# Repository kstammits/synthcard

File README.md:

# sc_Examples
demo and public synthcards

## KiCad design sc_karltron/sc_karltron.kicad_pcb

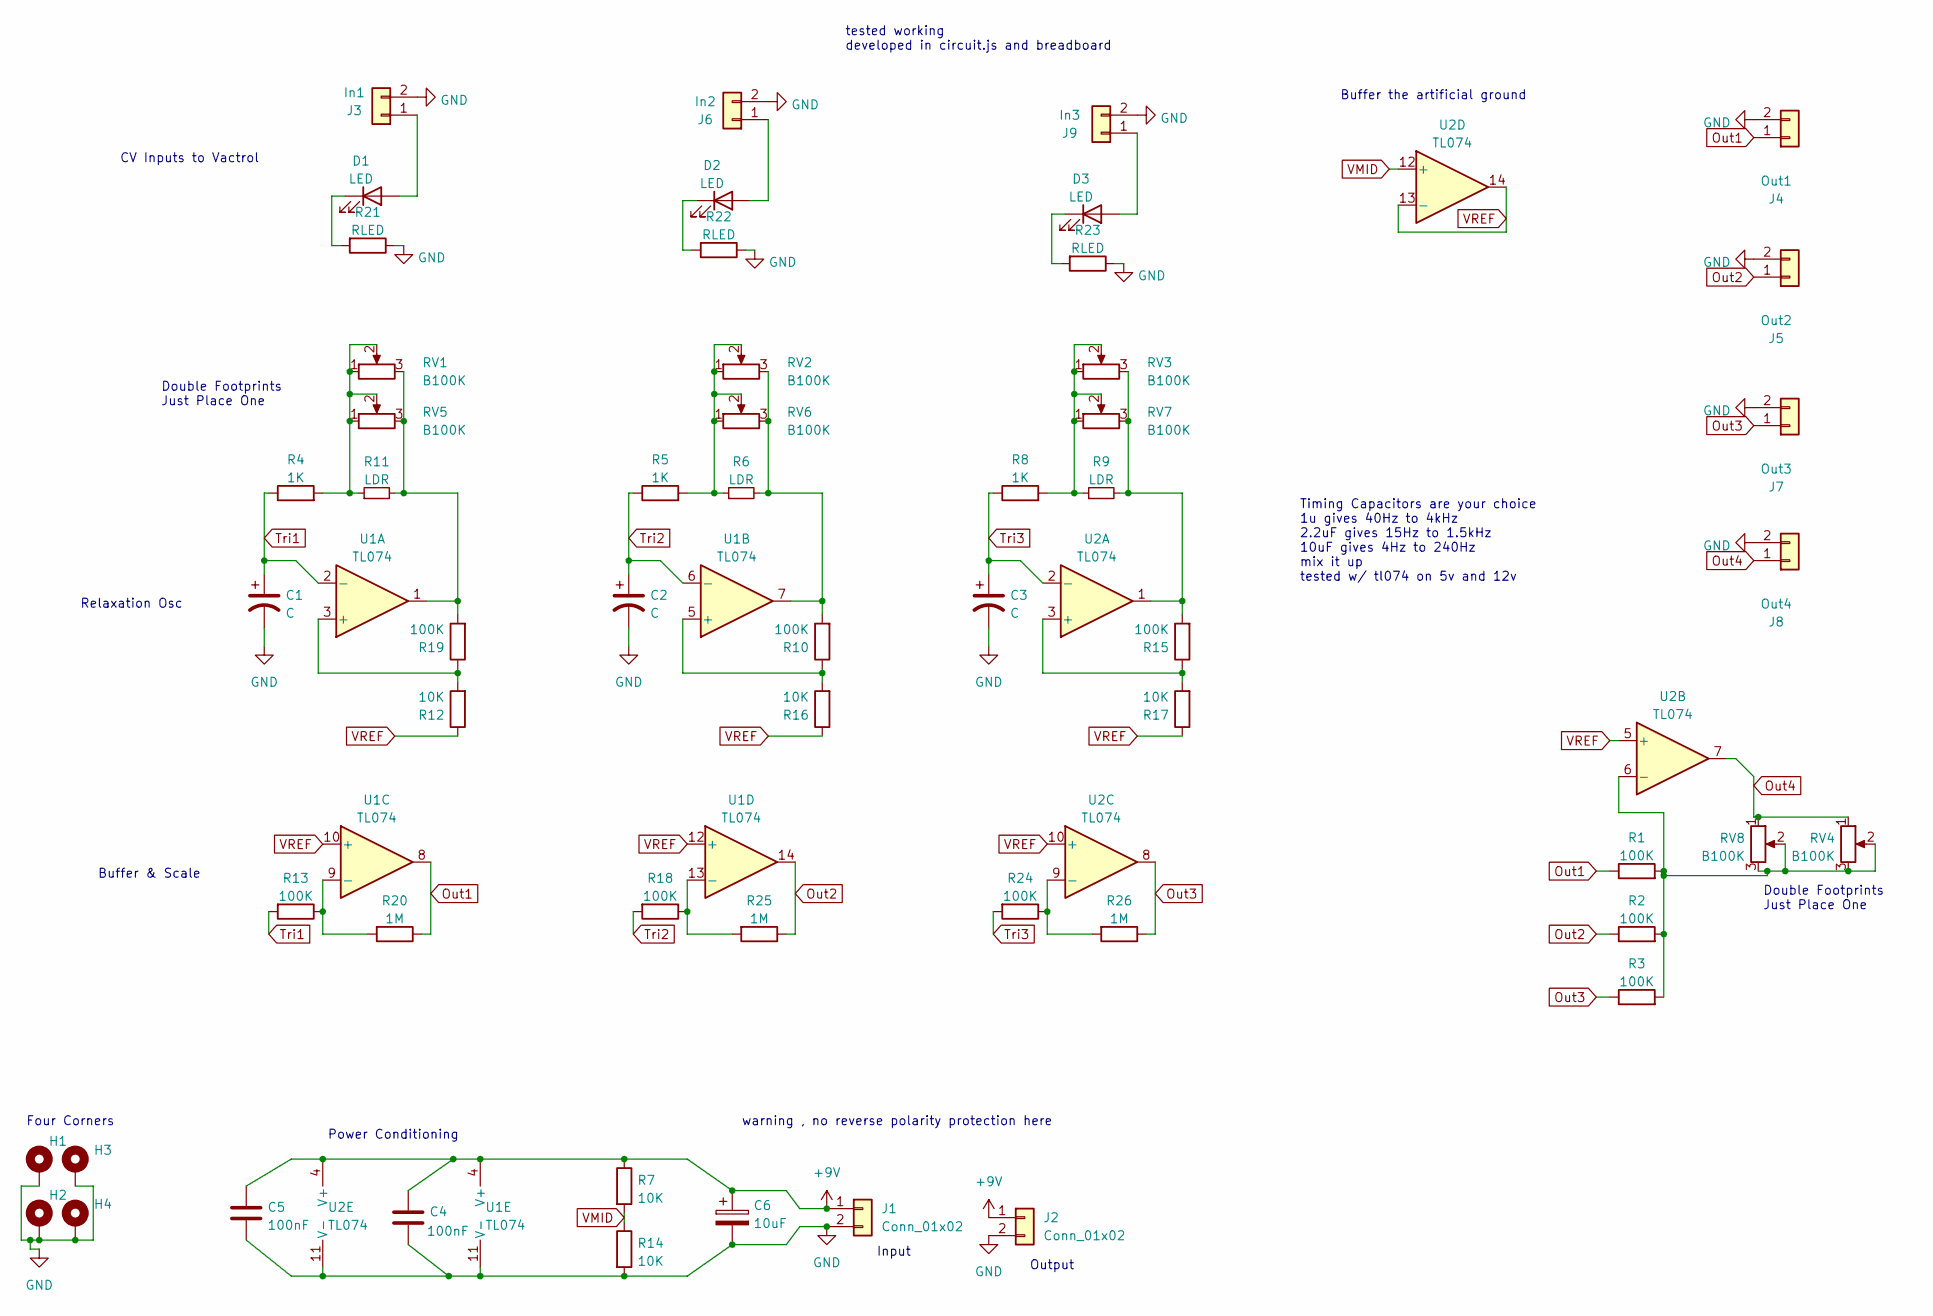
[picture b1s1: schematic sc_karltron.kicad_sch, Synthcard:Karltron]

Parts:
C1, C2, C3: C; C_Disc_D5.0mm_W2.5mm_P5.00mm
C4, C5: 100nF; C_Disc_D5.0mm_W2.5mm_P5.00mm
C6: 10uF; CP_Radial_D5.0mm_P2.50mm
D1, D2, D3: LED; LED_D5.0mm_Horizontal_O3.81mm_Z3.0mm
H1, H2, H3, H4: MountingHole_Pad; MountingHole_3.2mm_M3_Pad
J1, J2: Conn_01x02; PinHeader_1x02_P2.54mm_Horizontal
J3: In1; PinHeader_1x02_P2.54mm_Vertical
J4: Out1; PinHeader_1x02_P2.54mm_Vertical
J5: Out2; PinHeader_1x02_P2.54mm_Vertical
J6: In2; PinHeader_1x02_P2.54mm_Vertical
J7: Out3; PinHeader_1x02_P2.54mm_Vertical
J8: Out4; PinHeader_1x02_P2.54mm_Vertical
J9: In3; PinHeader_1x02_P2.54mm_Vertical
R1, R2, R3, R10, R13, R15, R18, R19, R24: 100K; R_Axial_DIN0207_L6.3mm_D2.5mm_P10.16mm_Horizontal
R4, R5, R8: 1K; R_Axial_DIN0207_L6.3mm_D2.5mm_P10.16mm_Horizontal
R6, R9, R11: LDR; R_Axial_DIN0204_L3.6mm_D1.6mm_P5.08mm_Horizontal
R7, R12, R14, R16, R17: 10K; R_Axial_DIN0207_L6.3mm_D2.5mm_P10.16mm_Horizontal
R20, R25, R26: 1M; R_Axial_DIN0207_L6.3mm_D2.5mm_P10.16mm_Horizontal
R21, R22, R23: RLED; R_Axial_DIN0207_L6.3mm_D2.5mm_P10.16mm_Horizontal
RV1, RV2, RV3, RV4: B100K; Potentiometer_ACP_CA9-H5_Horizontal
RV5, RV6, RV7, RV8: B100K; Potentiometer_Alpha_RD901F-40-00D_Single_Vertical
U1, U2: TL074; DIP-14_W7.62mm

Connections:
+9V: C4.1, C5.1, C6.1, J1.1, J2.1, R7.1, U1.4 (V+), U2.4 (V+)
GND: C1.2, C2.2, C3.2, C4.2, C5.2, C6.2, H1.1, H2.1, H3.1, H4.1, J1.2, J2.2, J3.2, J4.2, J5.2, J6.2, J7.2, J8.2, J9.2, R14.2, R21.1, R22.1, R23.1, U1.11 (V-), U2.11 (V-)
unnamed: D1.1 (K), R21.2
unnamed: D1.2 (A), J3.1
unnamed: D2.1 (K), R22.2
unnamed: D2.2 (A), J6.1
unnamed: D3.1 (K), R23.2
unnamed: D3.2 (A), J9.1
unnamed: R1.2, R2.2, R3.2, RV4.2, RV4.3, RV8.2, RV8.3, U2.6 (-)
unnamed: R5.2, R6.1, RV2.1, RV2.2, RV6.1, RV6.2
unnamed: R8.2, R9.1, RV3.1, RV3.2, RV7.1, RV7.2
unnamed: R12.2, R19.1, U1.3 (+)
unnamed: R13.1, R20.2, U1.9 (-)
unnamed: R4.2, R11.1, RV1.1, RV1.2, RV5.1, RV5.2
unnamed: R11.2, R19.2, RV1.3, RV5.3, U1.1
unnamed: R10.1, R16.2, U1.5 (+)
unnamed: R6.2, R10.2, RV2.3, RV6.3, U1.7
unnamed: R18.1, R25.2, U1.13 (-)
unnamed: R9.2, R15.2, RV3.3, RV7.3, U2.1
unnamed: R15.1, R17.2, U2.3 (+)
unnamed: R24.1, R26.2, U2.9 (-)
Out1: J4.1, R1.1, R20.1, U1.8
Out2: J5.1, R2.1, R25.1, U1.14
Out3: J7.1, R3.1, R26.1, U2.8
Out4: J8.1, RV4.1, RV8.1, U2.7
Tri1: C1.1, R4.1, R13.2, U1.2 (-)
Tri2: C2.1, R5.1, R18.2, U1.6 (-)
Tri3: C3.1, R8.1, R24.2, U2.2 (-)
VMID: R7.2, R14.1, U2.12 (+)
VREF: R12.1, R16.1, R17.1, U1.10 (+), U1.12 (+), U2.5 (+), U2.10 (+), U2.13 (-), U2.14

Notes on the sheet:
Double Footprints Just Place One
Input
CV Inputs to Vactrol
Output
tested working developed in circuit.js and breadboard
Buffer the artificial ground
Power Conditioning
Four Corners
Timing Capacitors are your choice 1u gives 40Hz to 4kHz 2.2uF gives 15Hz to 1.5kHz 10uF gives 4Hz to 240Hz mix it up tested w/ tl074 on 5v and 12v
Buffer & Scale
warning , no reverse polarity protection here
Relaxation Osc

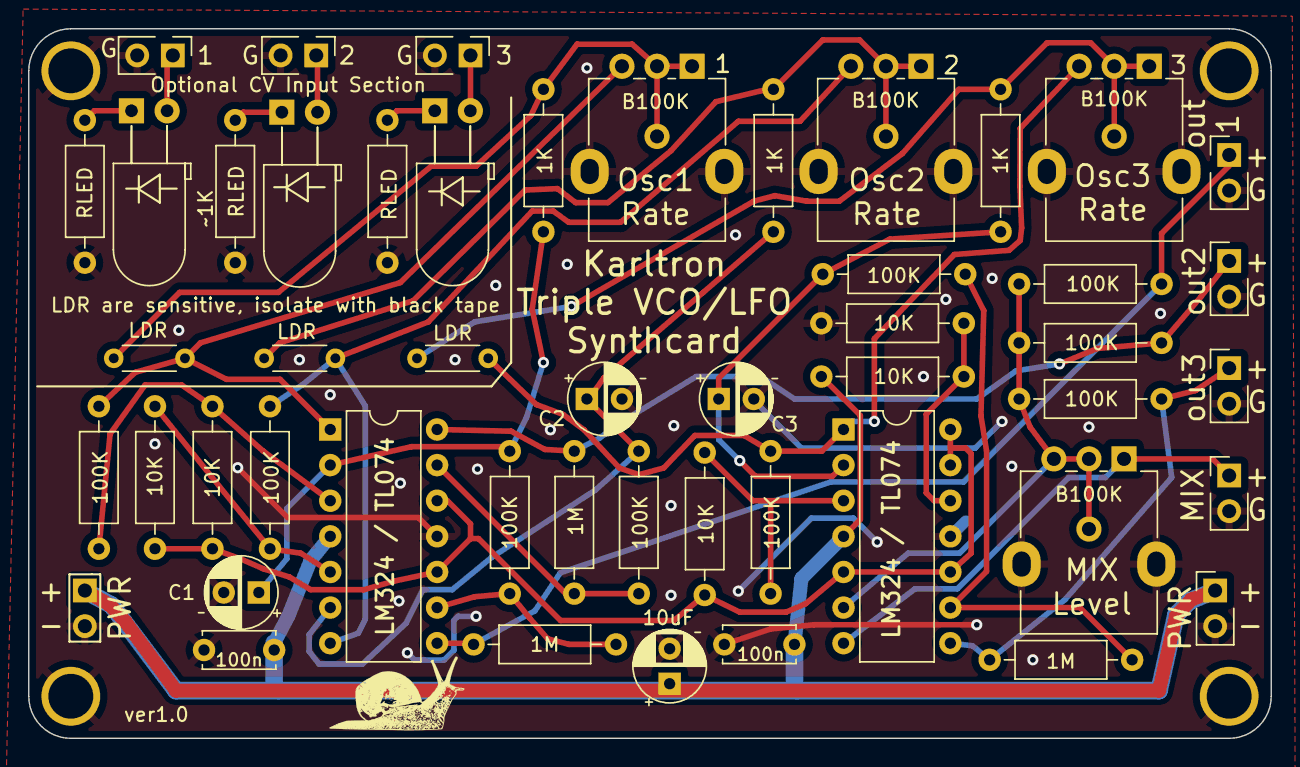
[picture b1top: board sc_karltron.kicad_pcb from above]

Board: 2 copper layers, 88.6 x 50.6 mm, 54 parts (1 on the bottom side), 30 nets.

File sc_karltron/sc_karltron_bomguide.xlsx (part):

Source: | /Users/karl/Workspace/KiCad/Shady/sc_Examples/sc_karltron/sc_karltron.kicad_sch
Date: | Thursday, February 16, 2023 at 06:49:55 PM
Tool: | Eeschema (6.0.7-1)-1
Generator: | /Applications/KiCad/KiCad.app/Contents/SharedSupport/plugins/bom_csv_grouped_by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
Component Count: | 58
Individual Components:
Item | Qty | Reference(s) | Value | LibPart | Footprint | Datasheet
 |  | C1 | C | Device:C_Polarized_US | Capacitor_THT:C_Disc_D5.0mm_W2.5mm_P5.00mm | ~
 |  | C2 | C | Device:C_Polarized_US | Capacitor_THT:C_Disc_D5.0mm_W2.5mm_P5.00mm | ~
 |  | C3 | C | Device:C_Polarized_US | Capacitor_THT:C_Disc_D5.0mm_W2.5mm_P5.00mm | ~
 |  | C4 | 100nF | Device:C | Capacitor_THT:C_Disc_D5.0mm_W2.5mm_P5.00mm | ~
 |  | C5 | 100nF | Device:C | Capacitor_THT:C_Disc_D5.0mm_W2.5mm_P5.00mm | ~
 |  | C6 | 10uF | Device:C_Polarized | Capacitor_THT:CP_Radial_D5.0mm_P2.50mm | ~
 |  | D1 | LED | Device:LED | LED_THT:LED_D5.0mm_Horizontal_O3.81mm_Z3.0mm | ~
 |  | D2 | LED | Device:LED | LED_THT:LED_D5.0mm_Horizontal_O3.81mm_Z3.0mm | ~
 |  | D3 | LED | Device:LED | LED_THT:LED_D5.0mm_Horizontal_O3.81mm_Z3.0mm | ~
 |  | H1 | MountingHole_Pad | Mechanical:MountingHole_Pad | MountingHole:MountingHole_3.2mm_M3_Pad | ~
 |  | H2 | MountingHole_Pad | Mechanical:MountingHole_Pad | MountingHole:MountingHole_3.2mm_M3_Pad | ~
 |  | H3 | MountingHole_Pad | Mechanical:MountingHole_Pad | MountingHole:MountingHole_3.2mm_M3_Pad | ~
 |  | H4 | MountingHole_Pad | Mechanical:MountingHole_Pad | MountingHole:MountingHole_3.2mm_M3_Pad | ~
 |  | J1 | Conn_01x02 | Connector_Generic:Conn_01x02 | Connector_PinHeader_2.54mm:PinHeader_1x02_P2.54mm_Horizontal | ~
 |  | J2 | Conn_01x02 | Connector_Generic:Conn_01x02 | Connector_PinHeader_2.54mm:PinHeader_1x02_P2.54mm_Horizontal | ~
 |  | J3 | In1 | Connector_Generic:Conn_01x02 | Connector_PinHeader_2.54mm:PinHeader_1x02_P2.54mm_Vertical | ~
 |  | J4 | Out1 | Connector_Generic:Conn_01x02 | Connector_PinHeader_2.54mm:PinHeader_1x02_P2.54mm_Vertical | ~
 |  | J5 | Out2 | Connector_Generic:Conn_01x02 | Connector_PinHeader_2.54mm:PinHeader_1x02_P2.54mm_Vertical | ~
 |  | J6 | In2 | Connector_Generic:Conn_01x02 | Connector_PinHeader_2.54mm:PinHeader_1x02_P2.54mm_Vertical | ~
 |  | J7 | Out3 | Connector_Generic:Conn_01x02 | Connector_PinHeader_2.54mm:PinHeader_1x02_P2.54mm_Vertical | ~
 |  | J8 | Out4 | Connector_Generic:Conn_01x02 | Connector_PinHeader_2.54mm:PinHeader_1x02_P2.54mm_Vertical | ~
 |  | J9 | In3 | Connector_Generic:Conn_01x02 | Connector_PinHeader_2.54mm:PinHeader_1x02_P2.54mm_Vertical | ~
 |  | R1 | 100K | Device:R | Resistor_THT:R_Axial_DIN0207_L6.3mm_D2.5mm_P10.16mm_Horizontal | ~
 |  | R2 | 100K | Device:R | Resistor_THT:R_Axial_DIN0207_L6.3mm_D2.5mm_P10.16mm_Horizontal | ~
 |  | R3 | 100K | Device:R | Resistor_THT:R_Axial_DIN0207_L6.3mm_D2.5mm_P10.16mm_Horizontal | ~
 |  | R4 | 1K | Device:R | Resistor_THT:R_Axial_DIN0207_L6.3mm_D2.5mm_P10.16mm_Horizontal | ~
 |  | R5 | 1K | Device:R | Resistor_THT:R_Axial_DIN0207_L6.3mm_D2.5mm_P10.16mm_Horizontal | ~
 |  | R6 | LDR | Device:R_Small | Resistor_THT:R_Axial_DIN0204_L3.6mm_D1.6mm_P5.08mm_Horizontal | ~
 |  | R7 | 10K | Device:R | Resistor_THT:R_Axial_DIN0207_L6.3mm_D2.5mm_P10.16mm_Horizontal | ~
 |  | R8 | 1K | Device:R | Resistor_THT:R_Axial_DIN0207_L6.3mm_D2.5mm_P10.16mm_Horizontal | ~
 |  | R9 | LDR | Device:R_Small | Resistor_THT:R_Axial_DIN0204_L3.6mm_D1.6mm_P5.08mm_Horizontal | ~
 |  | R10 | 100K | Device:R | Resistor_THT:R_Axial_DIN0207_L6.3mm_D2.5mm_P10.16mm_Horizontal | ~
 |  | R11 | LDR | Device:R_Small | Resistor_THT:R_Axial_DIN0204_L3.6mm_D1.6mm_P5.08mm_Horizontal | ~
 |  | R12 | 10K | Device:R | Resistor_THT:R_Axial_DIN0207_L6.3mm_D2.5mm_P10.16mm_Horizontal | ~
 |  | R13 | 100K | Device:R | Resistor_THT:R_Axial_DIN0207_L6.3mm_D2.5mm_P10.16mm_Horizontal | ~
 |  | R14 | 10K | Device:R | Resistor_THT:R_Axial_DIN0207_L6.3mm_D2.5mm_P10.16mm_Horizontal | ~
 |  | R15 | 100K | Device:R | Resistor_THT:R_Axial_DIN0207_L6.3mm_D2.5mm_P10.16mm_Horizontal | ~
 |  | R16 | 10K | Device:R | Resistor_THT:R_Axial_DIN0207_L6.3mm_D2.5mm_P10.16mm_Horizontal | ~
 |  | R17 | 10K | Device:R | Resistor_THT:R_Axial_DIN0207_L6.3mm_D2.5mm_P10.16mm_Horizontal | ~
 |  | R18 | 100K | Device:R | Resistor_THT:R_Axial_DIN0207_L6.3mm_D2.5mm_P10.16mm_Horizontal | ~
 |  | R19 | 100K | Device:R | Resistor_THT:R_Axial_DIN0207_L6.3mm_D2.5mm_P10.16mm_Horizontal | ~
 |  | R20 | 1M | Device:R | Resistor_THT:R_Axial_DIN0207_L6.3mm_D2.5mm_P10.16mm_Horizontal | ~
 |  | R21 | RLED | Device:R | Resistor_THT:R_Axial_DIN0207_L6.3mm_D2.5mm_P10.16mm_Horizontal | ~
 |  | R22 | RLED | Device:R | Resistor_THT:R_Axial_DIN0207_L6.3mm_D2.5mm_P10.16mm_Horizontal | ~
 |  | R23 | RLED | Device:R | Resistor_THT:R_Axial_DIN0207_L6.3mm_D2.5mm_P10.16mm_Horizontal | ~
 |  | R24 | 100K | Device:R | Resistor_THT:R_Axial_DIN0207_L6.3mm_D2.5mm_P10.16mm_Horizontal | ~
 |  | R25 | 1M | Device:R | Resistor_THT:R_Axial_DIN0207_L6.3mm_D2.5mm_P10.16mm_Horizontal | ~
 |  | R26 | 1M | Device:R | Resistor_THT:R_Axial_DIN0207_L6.3mm_D2.5mm_P10.16mm_Horizontal | ~
 |  | RV1 | B100K | Device:R_Potentiometer | Potentiometer_THT:Potentiometer_ACP_CA9-H5_Horizontal | ~
 |  | RV2 | B100K | Device:R_Potentiometer | Potentiometer_THT:Potentiometer_ACP_CA9-H5_Horizontal | ~
 |  | RV3 | B100K | Device:R_Potentiometer | Potentiometer_THT:Potentiometer_ACP_CA9-H5_Horizontal | ~
 |  | RV4 | B100K | Device:R_Potentiometer | Potentiometer_THT:Potentiometer_ACP_CA9-H5_Horizontal | ~
 |  | RV5 | B100K | Device:R_Potentiometer | Potentiometer_THT:Potentiometer_Alpha_RD901F-40-00D_Single_Vertical | ~
 |  | RV6 | B100K | Device:R_Potentiometer | Potentiometer_THT:Potentiometer_Alpha_RD901F-40-00D_Single_Vertical | ~
 |  | RV7 | B100K | Device:R_Potentiometer | Potentiometer_THT:Potentiometer_Alpha_RD901F-40-00D_Single_Vertical | ~
 |  | RV8 | B100K | Device:R_Potentiometer | Potentiometer_THT:Potentiometer_Alpha_RD901F-40-00D_Single_Vertical | ~
 |  | U1 | TL074 | Amplifier_Operational:TL074 | Package_DIP:DIP-14_W7.62mm | http://www.ti.com/lit/ds/symlink/tl071.pdf
 |  | U2 | TL074 | Amplifier_Operational:TL074 | Package_DIP:DIP-14_W7.62mm | http://www.ti.com/lit/ds/symlink/tl071.pdf
Collated Components:
Item | Qty | Reference(s) | Value | LibPart | Footprint | Datasheet
1 | 3 | C1, C2, C3 | C | Device:C_Polarized_US | Capacitor_THT:C_Disc_D5.0mm_W2.5mm_P5.00mm | ~
2 | 2 | C4, C5 | 100nF | Device:C | Capacitor_THT:C_Disc_D5.0mm_W2.5mm_P5.00mm | ~
3 | 1 | C6 | 10uF | Device:C_Polarized | Capacitor_THT:CP_Radial_D5.0mm_P2.50mm | ~
4 | 3 | D1, D2, D3 | LED | Device:LED | LED_THT:LED_D5.0mm_Horizontal_O3.81mm_Z3.0mm | ~
5 | 4 | H1, H2, H3, H4 | MountingHole_Pad | Mechanical:MountingHole_Pad | MountingHole:MountingHole_3.2mm_M3_Pad | ~
6 | 2 | J1, J2 | Conn_01x02 | Connector_Generic:Conn_01x02 | Connector_PinHeader_2.54mm:PinHeader_1x02_P2.54mm_Horizontal | ~
7 | 1 | J3 | In1 | Connector_Generic:Conn_01x02 | Connector_PinHeader_2.54mm:PinHeader_1x02_P2.54mm_Vertical | ~
8 | 1 | J4 | Out1 | Connector_Generic:Conn_01x02 | Connector_PinHeader_2.54mm:PinHeader_1x02_P2.54mm_Vertical | ~
9 | 1 | J5 | Out2 | Connector_Generic:Conn_01x02 | Connector_PinHeader_2.54mm:PinHeader_1x02_P2.54mm_Vertical | ~
10 | 1 | J6 | In2 | Connector_Generic:Conn_01x02 | Connector_PinHeader_2.54mm:PinHeader_1x02_P2.54mm_Vertical | ~
11 | 1 | J7 | Out3 | Connector_Generic:Conn_01x02 | Connector_PinHeader_2.54mm:PinHeader_1x02_P2.54mm_Vertical | ~
12 | 1 | J8 | Out4 | Connector_Generic:Conn_01x02 | Connector_PinHeader_2.54mm:PinHeader_1x02_P2.54mm_Vertical | ~
13 | 1 | J9 | In3 | Connector_Generic:Conn_01x02 | Connector_PinHeader_2.54mm:PinHeader_1x02_P2.54mm_Vertical | ~
14 | 9 | R1, R2, R3, R10, R13, R15, R18, R19, R24 | 100K | Device:R | Resistor_THT:R_Axial_DIN0207_L6.3mm_D2.5mm_P10.16mm_Horizontal | ~
15 | 3 | R4, R5, R8 | 1K | Device:R | Resistor_THT:R_Axial_DIN0207_L6.3mm_D2.5mm_P10.16mm_Horizontal | ~
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
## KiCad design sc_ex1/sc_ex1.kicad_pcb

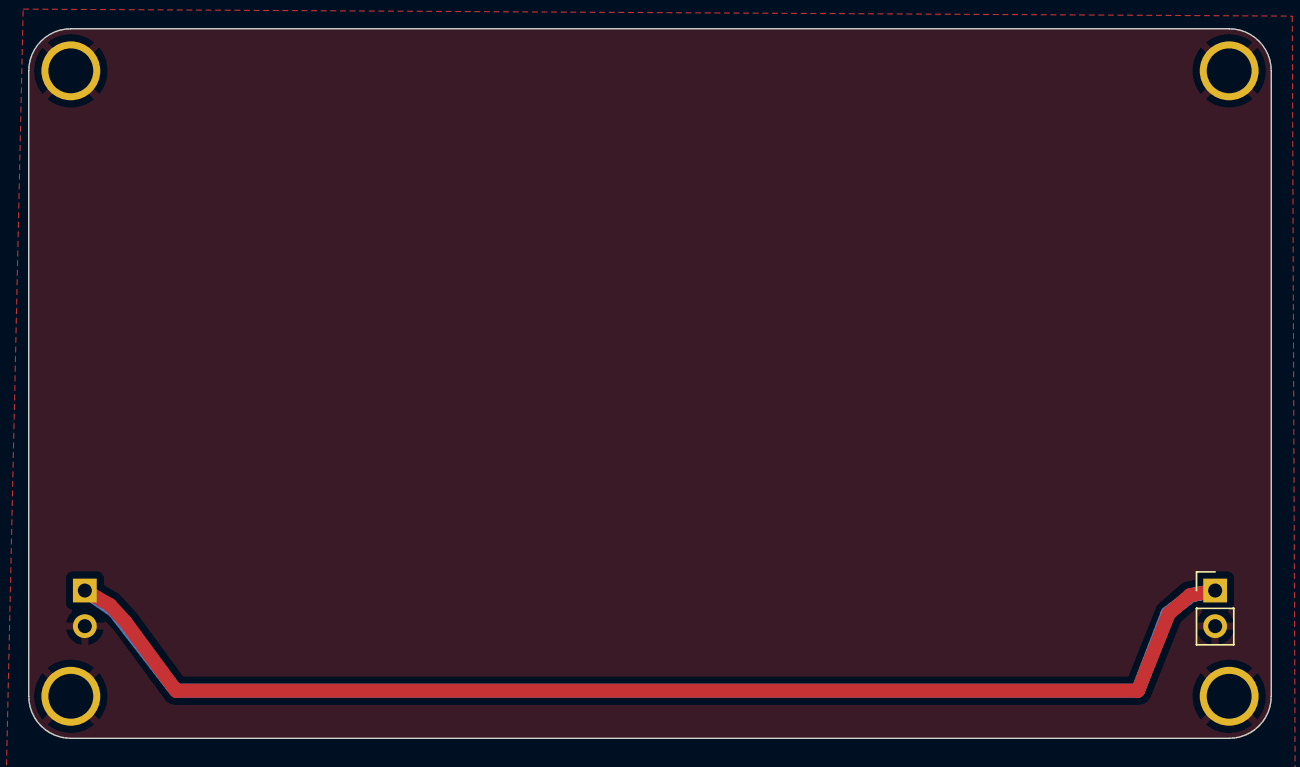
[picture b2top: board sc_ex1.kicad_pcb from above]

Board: 2 copper layers, 88.6 x 50.6 mm, 6 parts (1 on the bottom side), 2 nets.

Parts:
H1, H2, H3, H4: MountingHole_Pad; MountingHole_3.2mm_M3_Pad
J1, J2: Conn_01x02; PinHeader_1x02_P2.54mm_Vertical

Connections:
+9V: J1.1, J2.1
GND: H1.1, H2.1, H3.1, H4.1, J1.2, J2.2

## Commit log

2023-01-16 blank upload
    ex1 is a file with the outline you can use for your own.
2023-01-16 basic components
2023-01-17 working too
2023-01-17 halfway done
2023-01-19 completing
    v1.0 looks good to order. still untested
2023-01-19 adding notes
2023-01-20 printing
    first test - unproven
2023-02-07 after build
2023-02-17 adding some documentation
2023-05-15 post-render
    proven good
2023-05-19 tweaks, bugfix
    moved measurements and courtyards
2023-09-17 tweaks
    upd
2024-08-27 tweaks
